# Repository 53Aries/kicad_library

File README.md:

# kicad_library
Kicad footprints etc

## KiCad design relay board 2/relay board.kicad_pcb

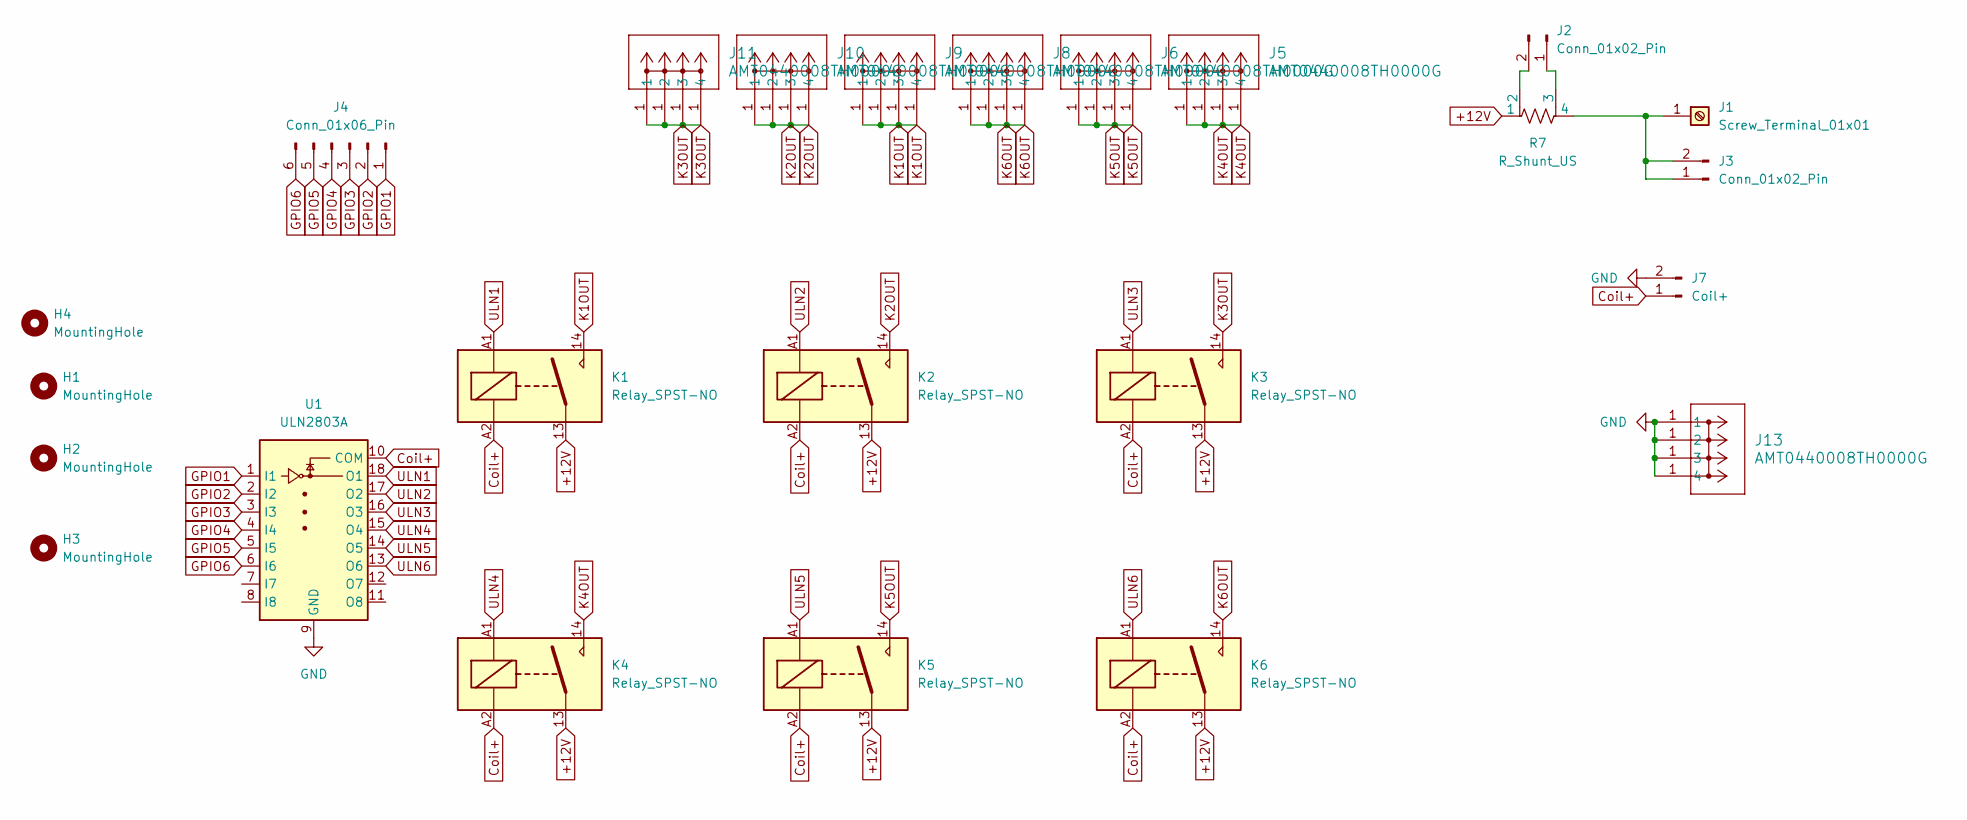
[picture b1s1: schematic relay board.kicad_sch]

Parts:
H1, H2, H3, H4: MountingHole; MountingHole_3.2mm_M3_DIN965
J1: Screw_Terminal_01x01; WP-BUTR_7461084
J2: Conn_01x02_Pin; JST_XH_B2B-XH-A_1x02_P2.50mm_Vertical
J3: Conn_01x02_Pin; TerminalBlock_Phoenix_MKDS-1,5-2-5.08_1x02_P5.08mm_Horizont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
J4: Conn_01x06_Pin; JST_XH_B6B-XH-A_1x06_P2.50mm_Vertical
J5, J6, J8, J9, J10, J11, J13: AMT0440008TH0000G; CONN_AMT0440008TH0000G_AMP
J7: Coil+; TerminalBlock_Phoenix_MKDS-1,5-2-5.08_1x02_P5.08mm_Horizont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
K1, K2, K3, K4, K5, K6: Relay_SPST-NO; J116F11AW
R7: R_Shunt_US; WSL4026_VIS
U1: ULN2803A; DIP-18_W7.62mm_LongPads

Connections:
+12V: K1.13, K2.13, K3.13, K4.13, K5.13, K6.13, R7.1
Coil+: J7.1, K1.A2, K2.A2, K3.A2, K4.A2, K5.A2, K6.A2, U1.10 (COM)
GND: J7.2, J13.1, U1.9 (GND)
GPIO1: J4.1, U1.1 (I1)
GPIO2: J4.2, U1.2 (I2)
GPIO3: J4.3, U1.3 (I3)
GPIO4: J4.4, U1.4 (I4)
GPIO5: J4.5, U1.5 (I5)
GPIO6: J4.6, U1.6 (I6)
K1OUT: J9.1, K1.14
K2OUT: J10.1, K2.14
K3OUT: J11.1, K3.14
K4OUT: J5.1, K4.14
K5OUT: J6.1, K5.14
K6OUT: J8.1, K6.14
unnamed: J1.1, J3.1, J3.2, R7.4
unnamed: J2.1, R7.3
unnamed: J2.2, R7.2
ULN1: K1.A1, U1.18 (O1)
ULN2: K2.A1, U1.17 (O2)
ULN3: K3.A1, U1.16 (O3)
ULN4: K4.A1, U1.15 (O4)
ULN5: K5.A1, U1.14 (O5)
ULN6: K6.A1, U1.13 (O6)

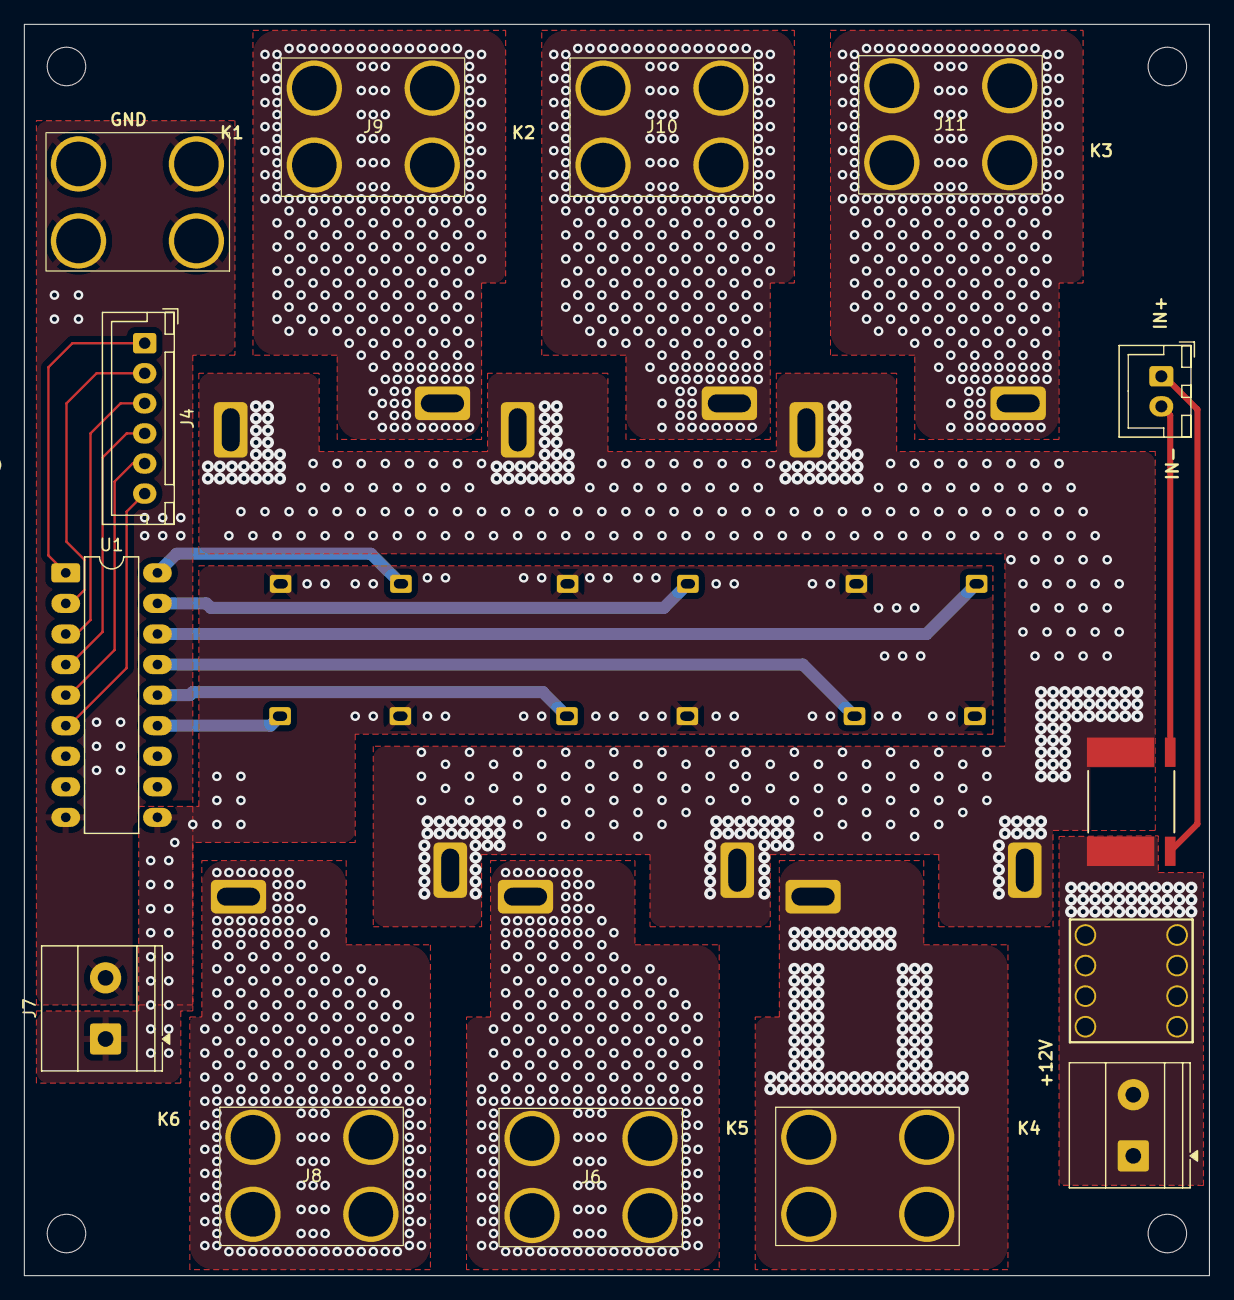
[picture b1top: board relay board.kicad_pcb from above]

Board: 2 copper layers, 98.5 x 104.0 mm, 24 parts (0 on the bottom side), 24 nets.

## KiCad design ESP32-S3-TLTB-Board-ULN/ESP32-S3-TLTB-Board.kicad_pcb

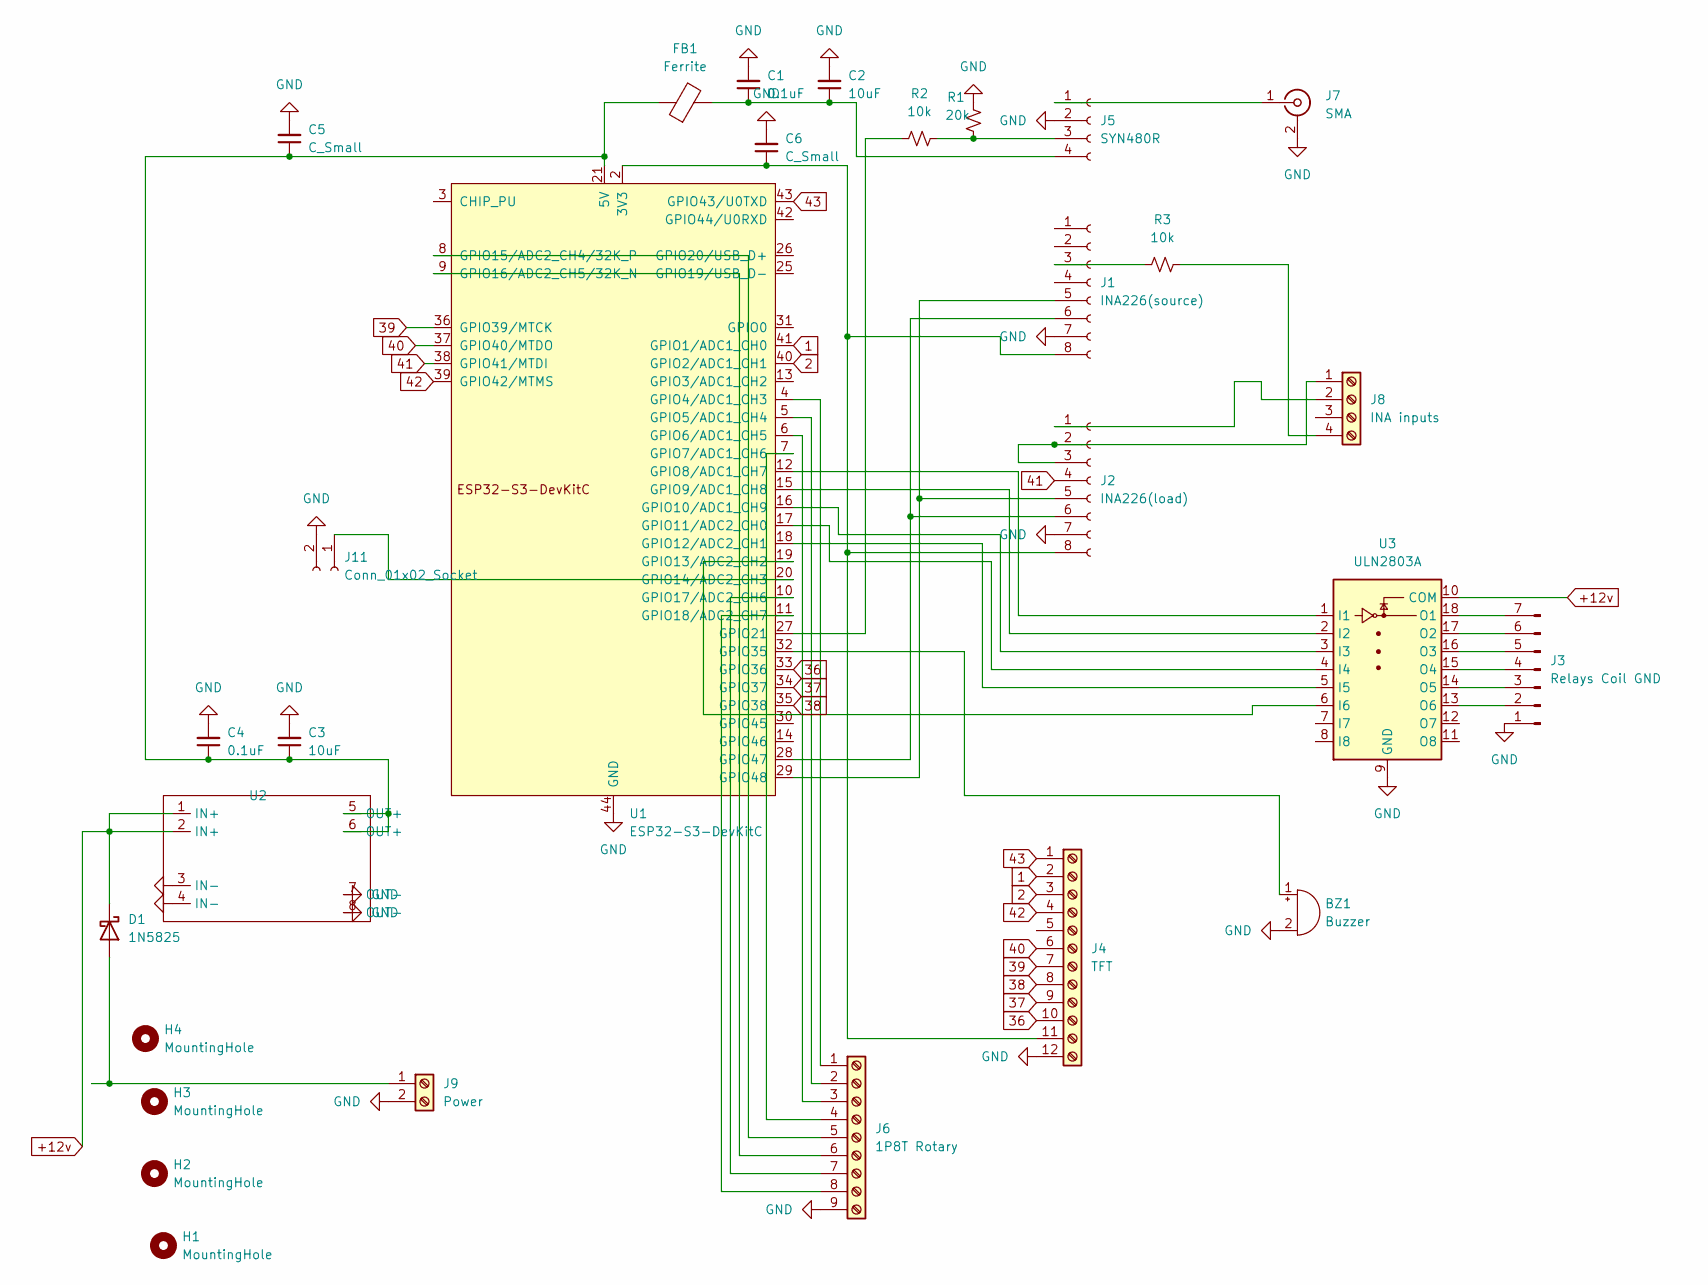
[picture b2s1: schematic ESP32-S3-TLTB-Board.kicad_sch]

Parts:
BZ1: Buzzer; Buzzer_12x9.5RM7.6
C1, C4: 0.1uF; C_Disc_D5.0mm_W2.5mm_P2.50mm
C2, C3: 10uF; C_Disc_D5.0mm_W2.5mm_P2.50mm
C5, C6: C_Small; CP_Radial_D6.3mm_P2.50mm
D1: 1N5825; D_DO-201AD_P15.24mm_Horizontal
FB1: Ferrite; L_Axial_L5.3mm_D2.2mm_P10.16mm_Horizontal_Vishay_IM-1
H1, H2, H3, H4: MountingHole; MountingHole_3.2mm_M3
J1: INA226(source); PinHeader_1x08_P2.54mm_Vertical
J2: INA226(load); PinHeader_1x08_P2.54mm_Vertical
J3: Relays Coil GND; JST_XH_B7B-XH-A_1x07_P2.50mm_Vertical
J4: TFT; JST_XH_B12B-XH-A_1x12_P2.50mm_Vertical
J5: SYN480R; PinHeader_1x04_P2.54mm_Vertical
J6: 1P8T Rotary; JST_XH_B9B-XH-A_1x09_P2.50mm_Vertical
J7: SMA; SMA_Amphenol_132134-16_Vertical
J8: INA inputs; JST_XH_B4B-XH-A_1x04_P2.50mm_Vertical
J9: Power; TerminalBlock_Phoenix_MKDS-3-2-5.08_1x02_P5.08mm_Horizontal
J11: Conn_01x02_Socket; JST_XH_B2B-XH-A_1x02_P2.50mm_Vertical
R1: 20k; R_Axial_DIN0207_L6.3mm_D2.5mm_P7.62mm_Horizontal
R2, R3: 10k; R_Axial_DIN0207_L6.3mm_D2.5mm_P7.62mm_Horizontal
U1: ESP32-S3-DevKitC
U2: 5v Buck module
U3: ULN2803A; DIP-18_W7.62mm

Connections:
1: J4.2, U1.41 (GPIO1/ADC1_CH0)
2: J4.3, U1.40 (GPIO2/ADC1_CH1)
36: J4.10, U1.33 (GPIO36)
37: J4.9, U1.34 (GPIO37)
38: J4.8, U1.35 (GPIO38)
39: J4.7, U1.36 (GPIO39/MTCK)
40: J4.6, U1.37 (GPIO40/MTDO)
41: J2.4, U1.38 (GPIO41/MTDI)
42: J4.4, U1.39 (GPIO42/MTMS)
43: J4.1, U1.43 (GPIO43/U0TXD)
+12v: D1.1 (K), U2.1 (IN+), U2.2 (IN+), U3.10 (COM)
GND: BZ1.2 (-), C1.2, C2.2, C3.2, C4.2, C5.2, C6.2, J1.7, J2.7, J3.1, J4.12, J5.2, J6.9, J7.2 (Ext), J9.2, J11.2, R1.1, U1.22 (GND), U1.23 (GND), U1.24 (GND), U1.44 (GND), U2.3 (IN-), U2.4 (IN-), U2.7 (OUT-), U2.8 (OUT-), U3.9 (GND)
unnamed: BZ1.1 (+), U1.32 (GPIO35)
unnamed: D1.2 (A), J9.1
unnamed: J1.3, R3.1
unnamed: J1.5, J2.5, U1.29 (GPIO48)
unnamed: J1.6, J2.6, U1.28 (GPIO47)
unnamed: C6.1, J1.8, J2.8, J4.11, U1.1 (3V3), U1.2 (3V3)
unnamed: J2.1, J8.2
unnamed: J2.2, J2.3, J8.1
unnamed: J3.2, U3.13 (O6)
unnamed: J3.3, U3.14 (O5)
unnamed: J3.4, U3.15 (O4)
unnamed: J3.5, U3.16 (O3)
unnamed: J3.6, U3.17 (O2)
unnamed: J3.7, U3.18 (O1)
unnamed: J5.1, J7.1 (In)
unnamed: J5.3, R1.2, R2.2
unnamed: C1.1, C2.1, FB1.2, J5.4
unnamed: J6.1, U1.4 (GPIO4/ADC1_CH3)
unnamed: J6.2, U1.5 (GPIO5/ADC1_CH4)
unnamed: J6.3, U1.6 (GPIO6/ADC1_CH5)
unnamed: J6.4, U1.7 (GPIO7/ADC1_CH6)
unnamed: J6.5, U1.8 (GPIO15/ADC2_CH4/32K_P)
unnamed: J6.6, U1.9 (GPIO16/ADC2_CH5/32K_N)
unnamed: J6.7, U1.10 (GPIO17/ADC2_CH6)
unnamed: J6.8, U1.11 (GPIO18/ADC2_CH7)
unnamed: J8.4, R3.2
unnamed: J11.1, U1.20 (GPIO14/ADC2_CH3)
unnamed: C3.1, C4.1, C5.1, FB1.1, U1.21 (5V), U2.5 (OUT+), U2.6 (OUT+)
unnamed: U1.12 (GPIO8/ADC1_CH7), U3.1 (I1)
unnamed: U1.15 (GPIO9/ADC1_CH8), U3.2 (I2)
unnamed: U1.16 (GPIO10/ADC1_CH9), U3.3 (I3)
unnamed: U1.17 (GPIO11/ADC2_CH0), U3.4 (I4)
unnamed: U1.18 (GPIO12/ADC2_CH1), U3.5 (I5)
unnamed: U1.19 (GPIO13/ADC2_CH2), U3.6 (I6)
unnamed: R2.1, U1.27 (GPIO21)

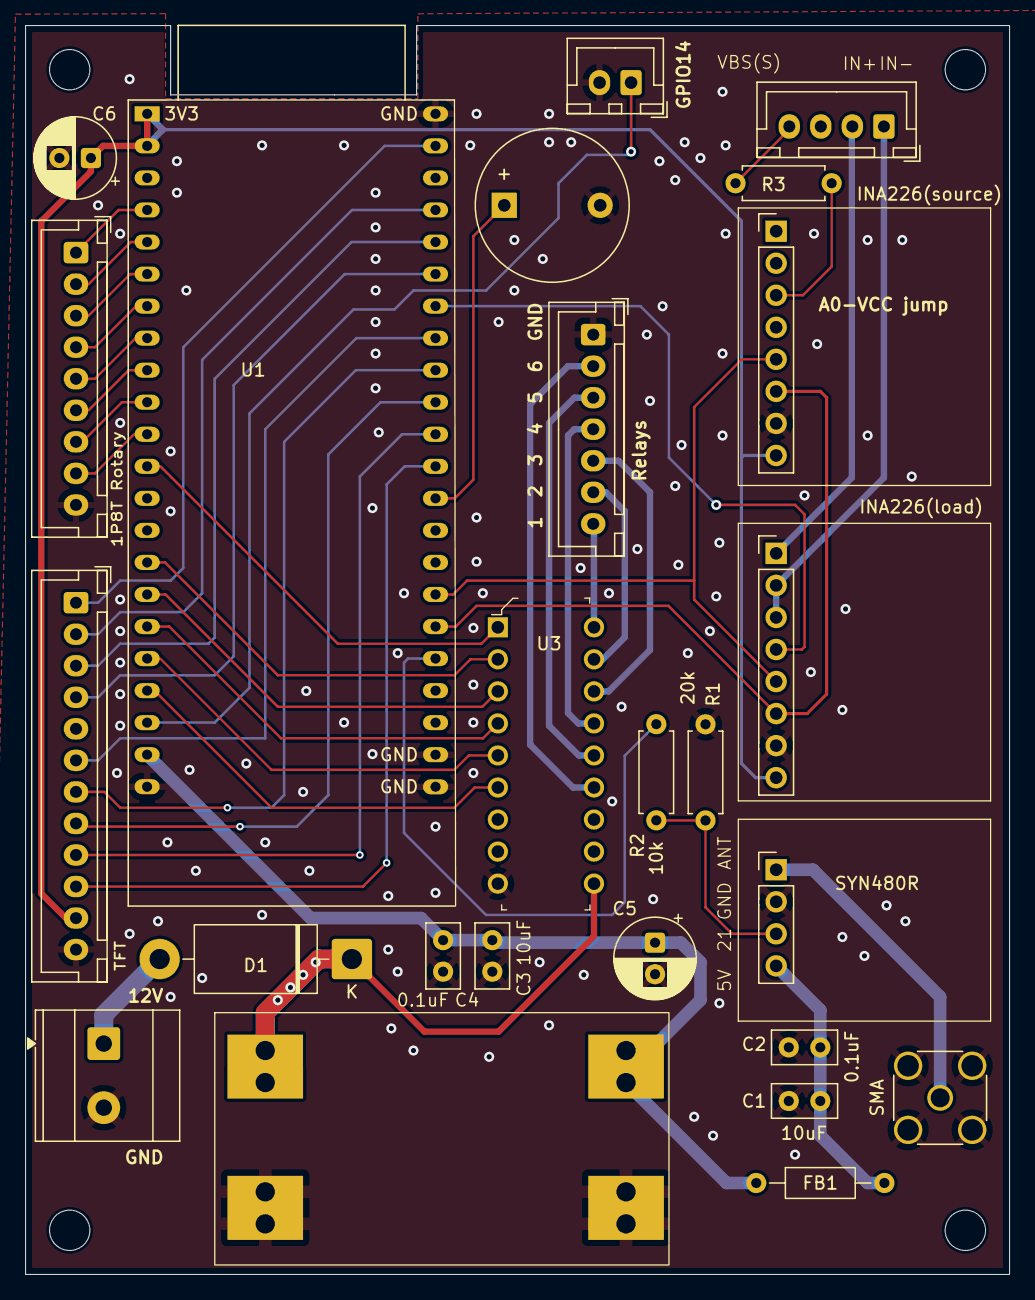
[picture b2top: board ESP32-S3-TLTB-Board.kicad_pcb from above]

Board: 2 copper layers, 78.0 x 99.0 mm, 29 parts (0 on the bottom side), 47 nets.

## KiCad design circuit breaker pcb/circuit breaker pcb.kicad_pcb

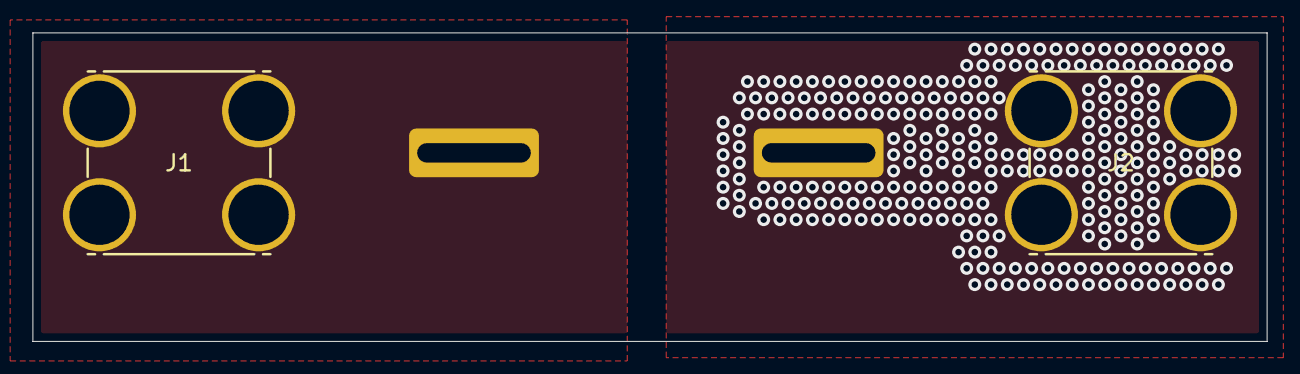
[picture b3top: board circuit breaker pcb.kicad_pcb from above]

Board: 2 copper layers, 76.0 x 19.0 mm, 3 parts (0 on the bottom side), 2 nets, no tracks yet.

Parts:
F1: Fuse; circuit_breaker
J1, J2: Conn_01x04_Socket; CONN_AMT0440008TH0000G_AMP

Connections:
unnamed: F1.1, J1.1, J1.2, J1.3, J1.4
unnamed: F1.2, J2.1, J2.2, J2.3, J2.4
